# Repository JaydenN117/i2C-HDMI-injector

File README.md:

# i2C-HDMI-injector, Code and casing. Never ordered PCB concept too.

Injects i2c signal to Dasung Paperlike Pro monitor through HDMI on modern macs, work in progress, have not ordered. 
Reversed engineered signal by simply reading with Oscilloscope.
Did not order kicad and would redo differently to make assembly easier but it was more of a learning excersize.

[Dual HDMI Breakout](https://www.amazon.com/Teansic-Connector-Female-Connectors-Transfer/dp/B0CKN298QF/ref=sr_1_1_pp?crid=25710WYSXEFZA&dib=eyJ2IjoiMSJ9.dwO7T6ixXoCnMktcI4ISrg5t2ZYv046Jhd_f-_575cwfZH8PASzIZ1QkvVDc3TXAZ940rQPXWw0ArziCfMW4-MjYdfgw0btn_IuL09l9dLIUx5mXClVs_e7FRnHXT6vxCDmulFsqz_H4WcrWaA_TG3Iee1x4hP0Mul1HF2X3idR6xNKcJq5uIi40qQCe-D3a8dM1sCyzfVeCcmkQAkY32a475oWU2K_FyxF2BzMX_qY.fWEpOz24M1QI76XVfhdoThRBkDU6-aeg679Ur-nxJVY&dib_tag=se&keywords=hdmi+breakout+board&qid=1758981994&sprefix=hdmi+breakout+board%2Caps%2C284&sr=8-1)
I ended up desoldering the pins to minimize footprint so perhaps a version [Without Presoldered headers](https://www.amazon.com/Cermant-Connector-Board%EF%BC%8C2-54-Connectors-Electronics/dp/B0DGT2GBF2/ref=sr_1_3?crid=1XA49GEN952SV&dib=eyJ2IjoiMSJ9.wnXFwrPHh2Wy17ayIPccoBIL8KxakjZDtvmHJkkTAlMDZeKj3Czd9LiIU-Kwsi7Nqi-2jN4aoVW34E_hqIrcMvuNJx7e_I-N3xs7jnSWvXC4oEtcZZHjoqG-L8XqdfTxVmkknt1iNr-1adhB3cEDv7u-sZVyfK5oB3dWg2uLBRj0hetf7i4Ps4rZKrzQFFSpVxv2FbYm0bVkLDBmiJiZs0Vt59FCVLn54sFATGShZ1A.F93ZgeioDOl6SbsPNRtD_hkZNoThlQJ6RECbz6dxoDw&dib_tag=se&keywords=HDMI+A+Connector+with+Test+PCB+Board&qid=1759920313&sprefix=hdmi+a+connector+with+test+pcb+board%2Caps%2C161&sr=8-3) would have been a better purchase

Refresh

Clear
<br>

Hardware: 5V level Pro Micro Soldered to HDMI breakout... Any 5V level AVR bar would work.

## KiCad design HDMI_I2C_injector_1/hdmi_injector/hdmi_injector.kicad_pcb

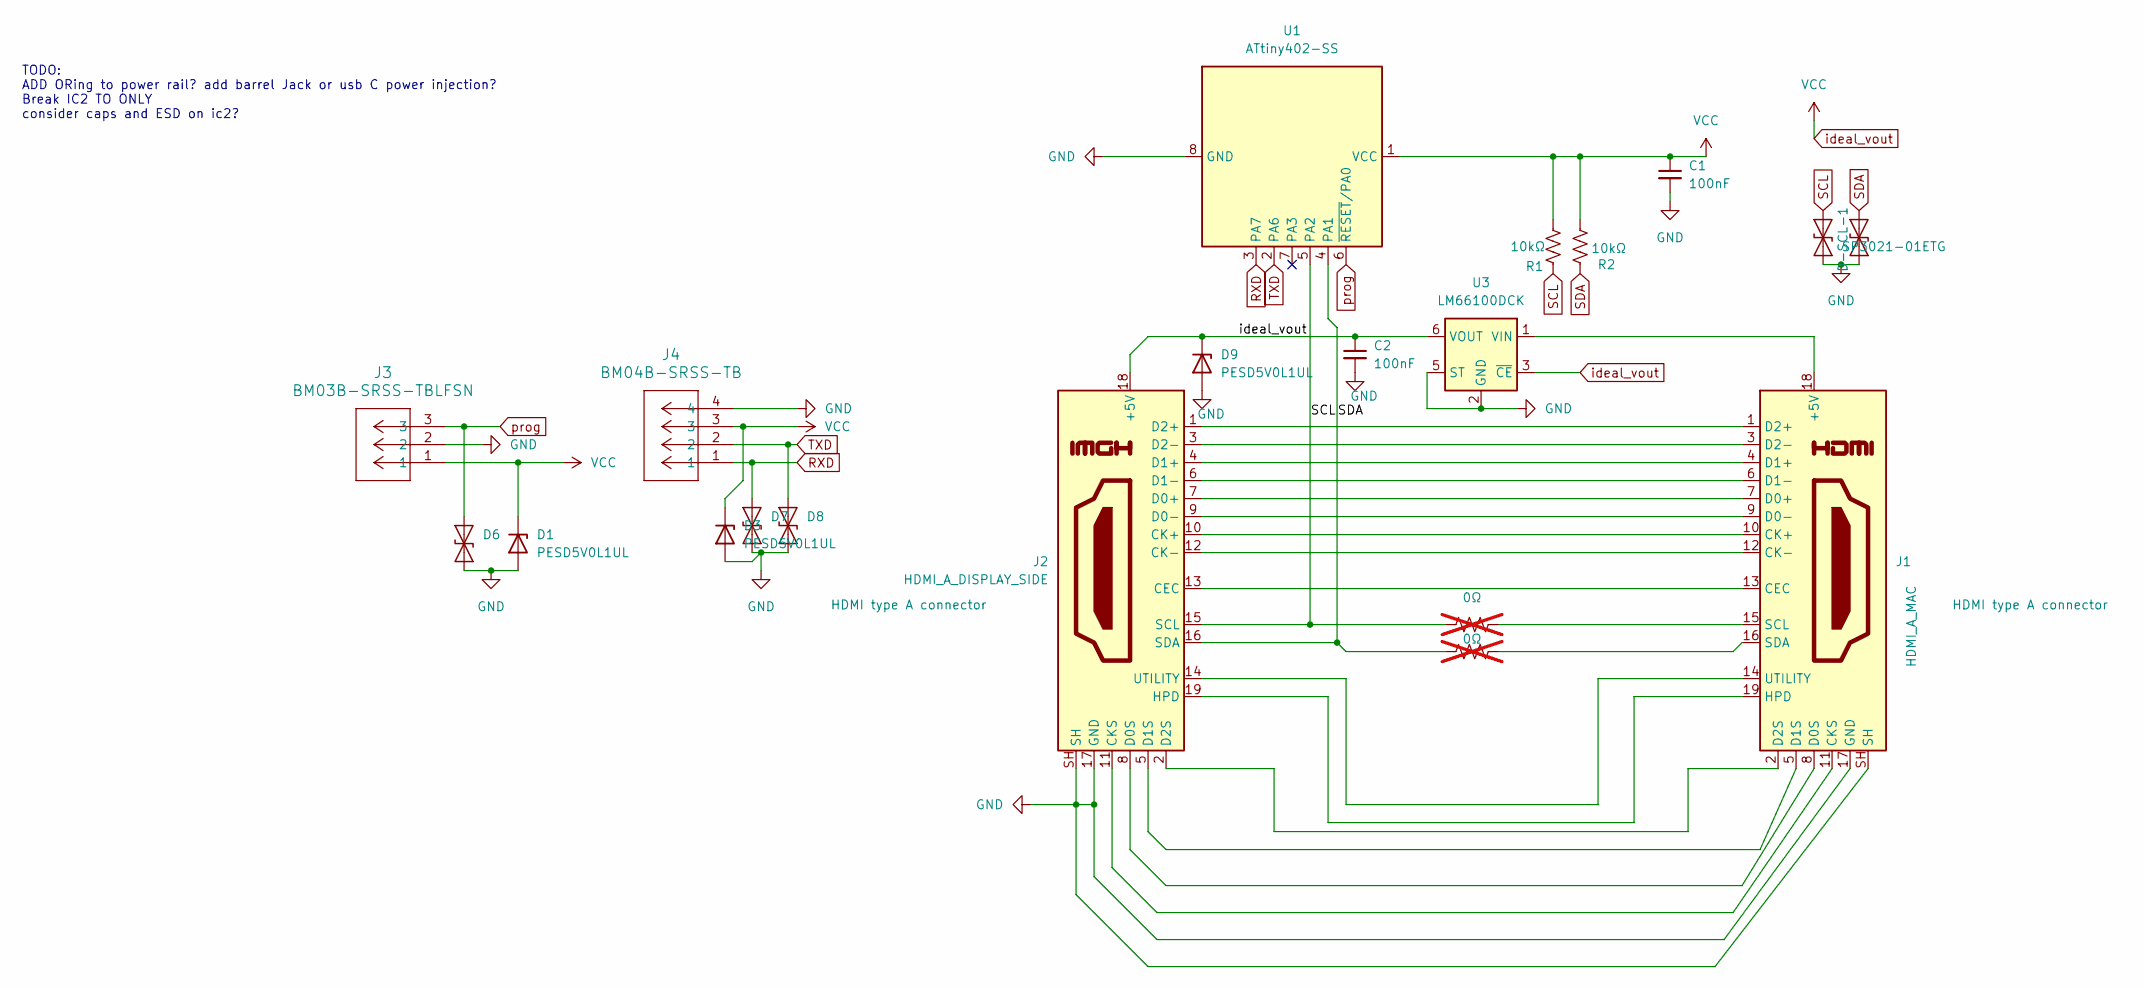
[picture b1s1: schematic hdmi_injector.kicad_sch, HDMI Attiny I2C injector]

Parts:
C1, C2: 100nF; C_0603_1608Metric_Pad1.08x0.95mm_HandSolder
D1, D3, D9: PESD5V0L1UL; D_SOD-882
D2, D6, D7, D8: SP3021-01ETG; D_SOD-882
D-SCL-1: SP3021-01ETG; D_SOD-882
J1: HDMI_A_MAC; HDMI-SMD_HDMI-GD-132PWB
J2: HDMI_A_DISPLAY_SIDE; HDMI-SMD_HDMI-GD-132PWB
J3: BM03B-SRSS-TBLFSN; CONN_BM03B-SRSS-TBLFSN_JST
J4: BM04B-SRSS-TB; CONN4_BM04B-SRSS_JST
R1, R2: 10kΩ; R_0603_1608Metric_Pad0.98x0.95mm_HandSolder
R3, R4: 0Ω; R_0603_1608Metric_Pad0.98x0.95mm_HandSolder; not fitted
U1: ATtiny402-SS; SOIC-8_3.9x4.9mm_P1.27mm
U3: LM66100DCK; SOT-363_SC-70-6

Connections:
GND: C1.2, C2.2, D1.2 (A), D2.1 (A1), D3.2 (A), D6.1 (A1), D7.1 (A1), D8.1 (A1), D9.2 (A), D-SCL-1.1 (A1), J1.17 (GND), J1.SH, J2.17 (GND), J2.SH, J3.2, J4.4, U1.8 (GND), U3.2 (GND), U3.5 (ST)
unnamed: J1.18 (+5V), U3.1 (VIN)
unnamed: J1.13 (CEC), J2.13 (CEC)
unnamed: J1.10 (CK+), J2.10 (CK+)
unnamed: J1.12 (CK-), J2.12 (CK-)
unnamed: J1.11 (CKS), J2.11 (CKS)
unnamed: J1.7 (D0+), J2.7 (D0+)
unnamed: J1.9 (D0-), J2.9 (D0-)
unnamed: J1.8 (D0S), J2.8 (D0S)
unnamed: J1.4 (D1+), J2.4 (D1+)
unnamed: J1.6 (D1-), J2.6 (D1-)
unnamed: J1.5 (D1S), J2.5 (D1S)
unnamed: J1.1 (D2+), J2.1 (D2+)
unnamed: J1.3 (D2-), J2.3 (D2-)
unnamed: J1.2 (D2S), J2.2 (D2S)
unnamed: J1.19 (HPD), J2.19 (HPD)
unnamed: J1.15 (SCL), R3.2
unnamed: J1.16 (SDA), R4.2
unnamed: J1.14 (UTILITY), J2.14 (UTILITY)
RXD: D7.2 (A2), J4.1, U1.3 (PA7)
SCL: D-SCL-1.2 (A2), J2.15 (SCL), R1.1, R3.1, U1.5 (PA2)
SDA: D2.2 (A2), J2.16 (SDA), R2.1, R4.1, U1.4 (PA1)
TXD: D8.2 (A2), J4.2, U1.2 (PA6)
ideal_vout: C1.1, C2.1, D1.1 (K), D3.1 (K), D9.1 (K), J2.18 (+5V), J3.1, J4.3, R1.2, R2.2, U1.1 (VCC), U3.3 (~CE), U3.6 (VOUT)
prog: D6.2 (A2), J3.3, U1.6 (~RESET/PA0)

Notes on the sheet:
TODO: ADD ORing to power rail? add barrel Jack or usb C power injection? Break IC2 TO ONLY consider caps and ESD on ic2?

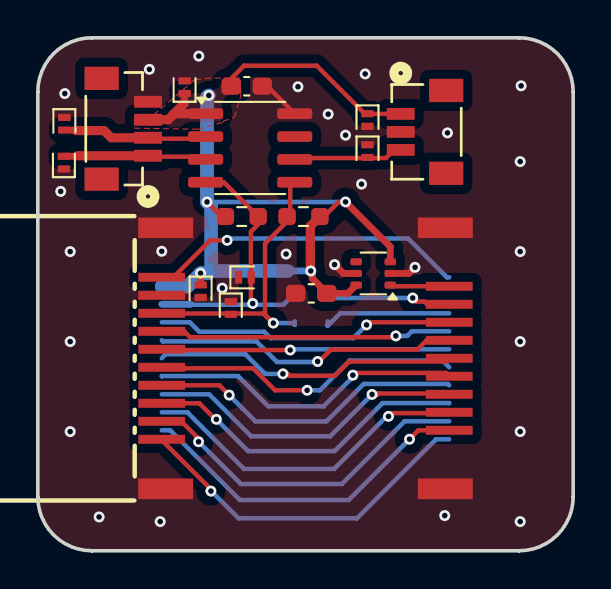
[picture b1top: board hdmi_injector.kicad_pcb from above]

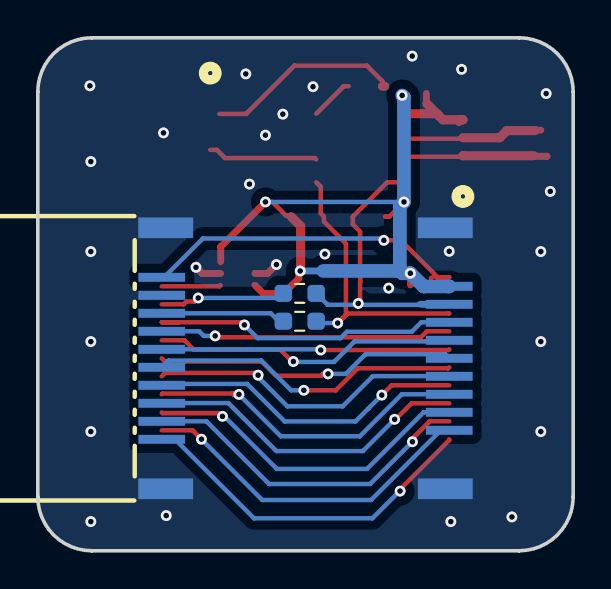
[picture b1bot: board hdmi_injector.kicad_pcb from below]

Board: 4 copper layers, 29.7 x 28.5 mm, 20 parts (3 on the bottom side), 25 nets.

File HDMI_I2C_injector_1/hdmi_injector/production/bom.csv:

Designator,Footprint,Quantity,Value,LCSC Part #
"C1, C2",0603,2,100nF,
"D-SCL-1, D2, D6, D7, D8",D_SOD-882,5,SP3021-01ETG,
"D1, D3, D9",D_SOD-882,3,PESD5V0L1UL,
J1,HDMI-SMD_HDMI-GD-132PWB,1,HDMI_A_MAC,
J2,HDMI-SMD_HDMI-GD-132PWB,1,HDMI_A_DISPLAY_SIDE,
J3,CONN_BM03B-SRSS-TBLFSN_JST,1,BM03B-SRSS-TBLFSN,
J4,CONN4_BM04B-SRSS_JST,1,BM04B-SRSS-TB,
"R1, R2",0603,2,10kΩ,
R4,0603,1,0Ω,
U1,SOIC-8_3.9x4.9mm_P1.27mm,1,ATtiny402-SS,
U3,SOT-363_SC-70-6,1,LM66100DCK,

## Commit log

2025-09-27 Added KiCAD files for v1
2025-10-08 CAD Files
    3D printed Casing and dummy pcb of the breakout board.
